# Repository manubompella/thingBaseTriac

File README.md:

# thingBaseTriac

The thingBaseTriac contains triac switching unit for dimming the bulbs

## Platform Features

  * 3.3V compatibility
  * 230V Switching
  
## Maintainers

The thingBaseTriac is maintained by thingTronics Innovations.

Main contributor:
 * Manohar Bompella @<manohar.bompella@thingtronics.com>
 * Suresh B @<suresh.b@thingtronics.com>
 * Lovelesh Patel @<lovelesh.patel@thingtronics.com>

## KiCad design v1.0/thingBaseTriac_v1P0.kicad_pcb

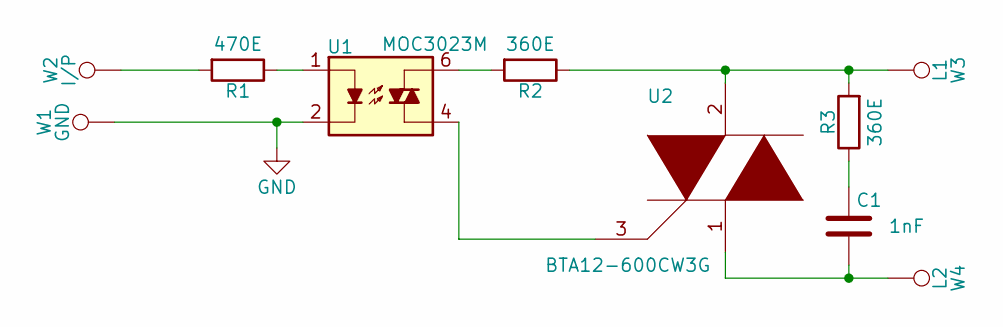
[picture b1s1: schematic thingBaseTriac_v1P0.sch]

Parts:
C1: 1nF; C_0805_HandSoldering
R1: 470E; C_0805_HandSoldering
R2, R3: 360E; R_1210_HandSoldering
U1: MOC3023M; DIP-6_W7.62mm
U2: BTA12-600CW3G; TO-220_Neutral123_Vertical_LargePads
W1: GND; SolderWirePad_single_0-8mmDrill
W2: I/P; SolderWirePad_single_0-8mmDrill
W3: L1; SolderWirePad_single_0-8mmDrill
W4: L2; SolderWirePad_single_0-8mmDrill

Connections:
GND: U1.2, W1.1
unnamed: C1.1, R3.1
unnamed: C1.2, U2.1, W4.1
unnamed: R1.1, U1.1
unnamed: R1.2, W2.1
unnamed: R2.1, R3.2, U2.2, W3.1
unnamed: R2.2, U1.6
unnamed: U1.4, U2.3

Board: 2 copper layers, 10 parts (0 on the bottom side), 8 nets, no tracks yet.

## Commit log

2017-02-03 :tada: Added .gitattributes & .gitignore files
2017-02-03 Added README, LICENSE and project files
2017-02-03 Added schematic, reference files and layout file
2017-02-03 schematic verified
